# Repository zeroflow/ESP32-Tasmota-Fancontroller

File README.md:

# ESP32 Tasmota-Fancontroller

## THIS MODULE HAS NOT YET BEEN BUILT, WORK IN PROGRESS
 
* 4x PWM Fan Output (3 Pin Fan Control not supported)
* 1x BME280 Header
* 1x Spare Header (3V3, GND, 4x IO)

## Tasmota Config

* Individual PWM Channel control
* Gamma correction OFF (0..100 = 0%..100% PWM, by default, Tasmota uses a [Gamma Table](https://tasmota.github.io/docs/Lights/#gamma-correction))

`Backlog Setoption68 1; LedTable 0`

## Tasmota32 Template

`{"NAME":"ESP32-Fancontroller","GPIO":[352,0,416,0,353,0,0,0,418,0,0,0,417,0,1,1,0,354,0,608,0,355,1,0,0,0,0,0,419,544,640,1,0,0,0,0],"FLAG":0,"BASE":1}`

| Function   | Pin |
| --------   | --- |
| Sense1     | IO_00 |
| PWM1       | IO_02 |
| Sense2     | IO_04 |
| PWM3       | IO_12 |
| PWM2       | IO_16 |
| Spare      | IO_18 |
| Spare      | IO_19 |
| Sense3     | IO_21 |
| BME280 SCL | IO_23 |
| Sense4     | IO_25 |
| Spare      | IO_26 |
| PWM4       | IO_32 |
| Link       | IO_33 |
| BME280 SDA | IO_34 |
| Spare      | IO_35 |

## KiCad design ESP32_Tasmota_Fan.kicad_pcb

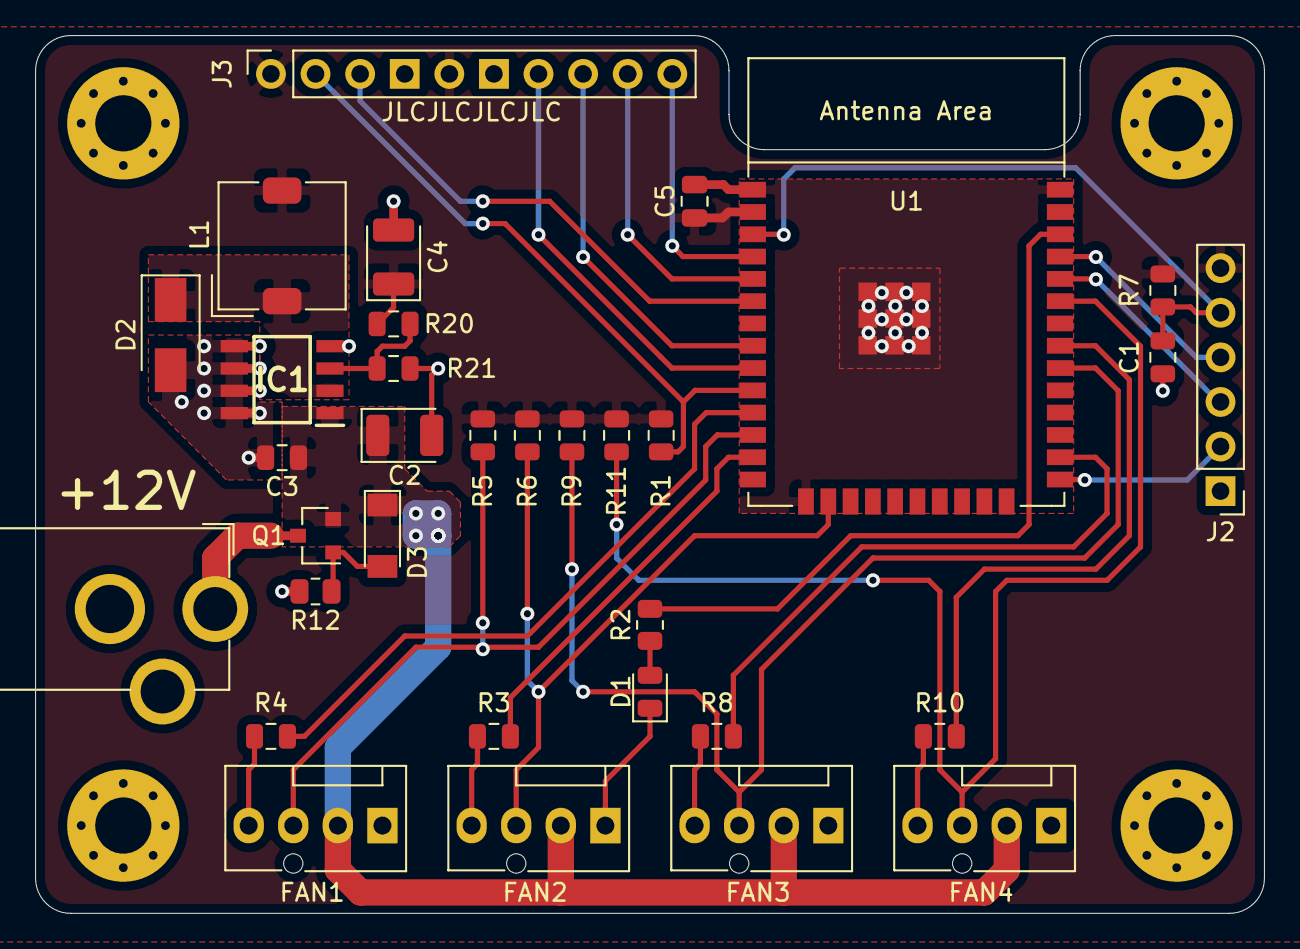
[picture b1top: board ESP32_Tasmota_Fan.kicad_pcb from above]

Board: 2 copper layers, 70.0 x 50.0 mm, 37 parts (0 on the bottom side), 31 nets.

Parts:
C1: 1uF/10V; C_0805_2012Metric
C2, C4: 330uF/6.3V; CP_EIA-3528-15_AVX-H
C3, C5: 1uF; C_0805_2012Metric
D1: LED; LED_0805_2012Metric
D2: 1N5820/SS34; D_SMA
D3: ZMM5V6; D_MiniMELF
FAN1, FAN2, FAN3, FAN4: Conn_01x04; FanPinHeader_1x04_P2.54mm_Vertical
H1, H2, H3, H4: MountingHole; MountingHole_3.2mm_M3_Pad_Via
IC1: XL1509-ADJE1; SOIC127P600X175-8N
J1: Conn_01x02_Female; BarrelJack_CUI_PJ-102AH_Horizontal
J2: Conn_01x06; PinHeader_1x06_P2.54mm_Vertical
J3: Conn_01x10; PinSocket_1x10_P2.54mm_Vertical
L1: 33uH; L_TDK_SLF7045
Q1: AO3401A; SOT-23
R1: 4k7; R_0805_2012Metric
R2: 1k; R_0805_2012Metric
R3, R4, R8, R10, R12: 100R; R_0805_2012Metric
R5, R6, R7, R9, R11: 10k; R_0805_2012Metric
R20: 2k7; R_0805_2012Metric
R21: 1k6; R_0805_2012Metric
U1: ESP32-WROOM-E; ESP32-WROOM-32E

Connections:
+3V3: C4.1, C5.1, J2.6, J3.1, J3.5, L1.2, R1.1, R5.1, R6.1, R7.1, R9.1, R11.1, R20.1, U1.2
+12V: C2.1, C3.1, D3.1, FAN1.2, FAN2.2, FAN3.2, FAN4.2, IC1.1, Q1.2
/DC/DC Buck/FB: IC1.3, R20.2, R21.1
/DC/DC Buck/OUTPUT: D2.1, IC1.2, L1.1
/ESP32 Core/EN: C1.1, J2.5, R7.2, U1.3
/ESP32 Core/IO0: J2.2, U1.25
/ESP32 Core/RX: J2.3, U1.34
/ESP32 Core/TX: J2.4, U1.35
/EXT1: J3.3, U1.6
/EXT2: J3.9, U1.5
/EXT3: J3.10, U1.4
/FAN 1/PWM_Ctrl: FAN1.4, R4.2
/LINK: R2.1, U1.36
/OneWire: J3.2, R1.2, U1.10
/PWM1: R4.1, U1.11
/PWM2: R3.1, U1.13
/PWM3: R8.1, U1.26
/PWM4: R10.1, U1.31
/SCL: J3.7, U1.9
/SDA: J3.8, U1.8
/SENSE1: FAN1.3, R5.2, U1.12
/SENSE2: FAN2.3, R6.2, U1.16
/SENSE3: FAN3.3, R9.2, U1.30
/SENSE4: FAN4.3, R11.2, U1.33
/VIN: J1.1, Q1.3
/sheet61958B6B/PWM_Ctrl: FAN4.4, R10.2
/sheet619566BF/PWM_Ctrl: FAN2.4, R3.2
/sheet61957927/PWM_Ctrl: FAN3.4, R8.2
GND: C1.2, C2.2, C3.2, C4.2, C5.2, D1.1, D2.2, FAN1.1, FAN2.1, FAN3.1, FAN4.1, IC1.4, IC1.5, IC1.6, IC1.7, IC1.8, J1.2, J2.1, J3.4, J3.6, R12.2, R21.2, U1.1, U1.15, U1.38, U1.39
unnamed: D1.2, R2.2
unnamed: D3.2, Q1.1, R12.1

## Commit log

2021-03-27 Initial Drop
    First version, still waiting for verification of DC input jack availability
2021-03-28 Production Version
2021-04-29 Move I2C Pins for BME280
    IO34 can only do input, so it is not suitable for I2C
2021-11-07 First step for new design
    split up design into multiples
    added voltage regulator available at JLCPCB
2021-11-07 First layouting
2021-11-10 First iteration with new ES32 - but not S2
2021-11-10 Include fabrication outputs
2021-11-10 Add JLC template
2021-11-14 Version open for review
